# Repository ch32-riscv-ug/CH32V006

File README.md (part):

# CH32V006

<!-- This file is generated from ch32-riscv-ug/ch32-device-data (index/ + evidence/ + pipeline/build/build_readme.py). Edit there, not here. -->

[Choose a part](#product-comparison) &middot; [Documents](#documents) &middot; [Pin maps](#pin-maps--alternate-functions) &middot; [Pin viewer](https://ch32-riscv-ug.github.io/ch32-device-data/pins.html?chip=CH32M007) &middot; [Errata](#errata) &middot; [Examples](#evt-examples) &middot; [Address map](#address-map)

## Quick start

Programming and debug: **1-wire SDI** (WCH-Link, `Serial Debug Interface`).

### Debug / serial defaults

Where these land **without writing a remap register**. SWD is live at reset; the UART pads are not -- the pin must still be put into alternate-function mode. See `route` in evidence/README.ja.md.

| Series | SWDIO | SWCLK | UART TX | UART RX |
|---|---|---|---|---|
| CH32M007 | PD1 | PB3 | PD5 (USART1) | PD6 (USART1); PB3 (USART2) |
| CH32V002 | PD1 | - | PD5 (USART1) | PD6 (USART1) |
| CH32V004 | PD1 | - | PD5 (USART1) | PD6 (USART1) |
| CH32V005 | PD1 | PB3 | PD5 (USART1) | PD6 (USART1); PB3 (USART2) |
| CH32V006 | PD1 | PB3 | PD5 (USART1); PA7 (USART2) | PD6 (USART1); PB3 (USART2) |
| CH32V007 | PD1 | PB3 | PD5 (USART1); PA7 (USART2) | PD6 (USART1); PB3 (USART2) |

### Datasheets and reference manual

- CH32V002DS0.PDF (datasheet): [English](https://ch32-riscv-ug.github.io/CH32V006/datasheet_en/CH32V002DS0.PDF) · [中文](https://ch32-riscv-ug.github.io/CH32V006/datasheet_zh/CH32V002DS0.PDF)
- CH32V004DS0.PDF (datasheet): [English](https://ch32-riscv-ug.github.io/CH32V006/datasheet_en/CH32V004DS0.PDF) · [中文](https://ch32-riscv-ug.github.io/CH32V006/datasheet_zh/CH32V004DS0.PDF)
- CH32V006DS0.PDF (datasheet): [English](https://ch32-riscv-ug.github.io/CH32V006/datasheet_en/CH32V006DS0.PDF) · [中文](https://ch32-riscv-ug.github.io/CH32V006/datasheet_zh/CH32V006DS0.PDF)
- CH32V006DS2.PDF (datasheet): [中文](https://ch32-riscv-ug.github.io/CH32V006/datasheet_zh/CH32V006DS2.PDF)
- CH32V007DS0.PDF (datasheet): [English](https://ch32-riscv-ug.github.io/CH32V006/datasheet_en/CH32V007DS0.PDF) · [中文](https://ch32-riscv-ug.github.io/CH32V006/datasheet_zh/CH32V007DS0.PDF)
- CH32V00XRM.PDF (reference manual): [English](https://ch32-riscv-ug.github.io/CH32V006/datasheet_en/CH32V00XRM.PDF) · [中文](https://ch32-riscv-ug.github.io/CH32V006/datasheet_zh/CH32V00XRM.PDF)

## Series

Flash and SRAM list every value the series has; more than one means it varies by part number, and the per-part values are in the comparison table below.

| Series | Core | ISA | Flash | SRAM | Main clock | VDD | Packages | Products | Official |
|---|---|---|---|---|---|---|---|---|---|
| **CH32M007** | QingKe V2C | RV32EmC | 62K | 8K | 48 MHz | 2.0-5.5V | QFN26C3,QFN32,QSOP24,QSOP28 | 4 | [en](https://www.wch-ic.com/products/CH32M007.html) / [zh](https://www.wch.cn/products/CH32M007.html) |
| **CH32V002** | QingKe V2C | RV32EmC | 16K | 4K | 48 MHz | 2.0-5.5V | QFN12,QFN20,SOP16,SOP8,TSSOP20 | 5 | [en](https://www.wch-ic.com/products/CH32V002.html) / [zh](https://www.wch.cn/products/CH32V002.html) |
| **CH32V004** | QingKe V2C | RV32EmC | 32K | 6K | 48 MHz | 2.7-5.5V | QFN20L,TSSOP20 | 2 | [en](https://www.wch-ic.com/products/CH32V004.html) / [zh](https://www.wch.cn/products/CH32V004.html) |
| **CH32V005** | QingKe V2C | RV32EmC | 32K | 6K | 48 MHz | 2.0-5.5V | QFN12,QFN20,QSOP24,TSSOP20 | 4 | [en](https://www.wch-ic.com/products/CH32V005.html) / [zh](https://www.wch.cn/products/CH32V005.html) |
| **CH32V006** | QingKe V2C | RV32EmC | 16K/62K | 4K/8K | 48 MHz | 2.0-5.5V | QFN12,QFN20,QFN32,QSOP24,TSSOP20 | 8 | [en](https://www.wch-ic.com/products/CH32V006.html) / [zh](https://www.wch.cn/products/CH32V006.html) |
| **CH32V007** | QingKe V2C | RV32EmC | 62K | 8K | 48 MHz | 2.0-5.5V | QFN32,QSOP24 | 4 | [en](https://www.wch-ic.com/products/CH32V007.html) / [zh](https://www.wch.cn/products/CH32V007.html) |

## Product comparison

### CH32M007 product comparison

Only the 4 rows that differ between these 4 products; the other 14 are the same for all of them.

| | [CH32M007&#8203;E8R6](https://ch32-riscv-ug.github.io/ch32-device-data/pins.html?chip=CH32M007E8R6)&#8203;(QSOP24) | [CH32M007&#8203;E8U7](https://ch32-riscv-ug.github.io/ch32-device-data/pins.html?chip=CH32M007E8U7)&#8203;(QFN26C3) | [CH32M007&#8203;G8R6](https://ch32-riscv-ug.github.io/ch32-device-data/pins.html?chip=CH32M007G8R6)&#8203;(QSOP28) | [CH32M007&#8203;K8U7](https://ch32-riscv-ug.github.io/ch32-device-data/pins.html?chip=CH32M007K8U7)&#8203;(QFN32) |
|---|---|---|---|---|
| **GPIO** | 15 | 16 | 12 | 17 |
| **Temperature** | -40..85C | -40..105C | -40..85C | -40..105C |
| Three-phase pre-drive Voltage | 24V | 24V | 48V | 48V |
| Structure | P+N | P+N | N+N | N+N |

<details><summary>All 18 rows</summary>

| | [CH32M007&#8203;E8R6](https://ch32-riscv-ug.github.io/ch32-device-data/pins.html?chip=CH32M007E8R6)&#8203;(QSOP24) | [CH32M007&#8203;E8U7](https://ch32-riscv-ug.github.io/ch32-device-data/pins.html?chip=CH32M007E8U7)&#8203;(QFN26C3) | [CH32M007&#8203;G8R6](https://ch32-riscv-ug.github.io/ch32-device-data/pins.html?chip=CH32M007G8R6)&#8203;(QSOP28) | [CH32M007&#8203;K8U7](https://ch32-riscv-ug.github.io/ch32-device-data/pins.html?chip=CH32M007K8U7)&#8203;(QFN32) |
|---|---|---|---|---|
| **Flash** | 62K | 62K | 62K | 62K |
| **SRAM** | 8K | 8K | 8K | 8K |
| **GPIO** | 15 | 16 | 12 | 17 |
| **Temperature** | -40..85C | -40..105C | -40..85C | -40..105C |
| ADTM | 1 | 1 | 1 | 1 |
| GPTM | 1 | 1 | 1 | 1 |
| Streamlined timer | 1 | 1 | 1 | 1 |
| Watchdog | 2 | 2 | 2 | 2 |
| Three-phase pre-drive Voltage | 24V | 24V | 48V | 48V |
| Structure | P+N | P+N | N+N | N+N |
| ADC | 7+2 | 7+2 | 7+2 | 7+2 |
| Touch-key button | 7 | 7 | 7 | 7 |
| OPA | 1 | 1 | 1 | 1 |
| OPA Polling | 3 | 3 | 3 | 3 |
| CMP | 2 | 2 | 2 | 2 |
| Serial port | 2 | 2 | 2 | 2 |
| I2C | 1 | 1 | 1 | 1 |
| SPI | 1 | 1 | 1 | 1 |

</details>

### CH32V002 product comparison

Only the 3 rows that differ between these 5 products; the other 8 are the same for all of them.

| | [CH32V002&#8203;A4M6](https://ch32-riscv-ug.github.io/ch32-device-data/pins.html?chip=CH32V002A4M6)&#8203;(SOP16) | [CH32V002&#8203;D4U6](https://ch32-riscv-ug.github.io/ch32-device-data/pins.html?chip=CH32V002D4U6)&#8203;(QFN12) | [CH32V002&#8203;F4P6](https://ch32-riscv-ug.github.io/ch32-device-data/pins.html?chip=CH32V002F4P6)&#8203;(TSSOP20) | [CH32V002&#8203;F4U6](https://ch32-riscv-ug.github.io/ch32-device-data/pins.html?chip=CH32V002F4U6)&#8203;(QFN20) | [CH32V002&#8203;J4M6](https://ch32-riscv-ug.github.io/ch32-device-data/pins.html?chip=CH32V002J4M6)&#8203;(SOP8) |
|---|---|---|---|---|---|
| **GPIO** | 14 | 11 | 18 | 18 | 6 |
| ADC | 6+2 | 4+2 | 8+2 | 8+2 | 6+2 |
| SPI | 1 | - | 1 | 1 | - |

<details><summary>All 11 rows</summary>

| | [CH32V002&#8203;A4M6](https://ch32-riscv-ug.github.io/ch32-device-data/pins.html?chip=CH32V002A4M6)&#8203;(SOP16) | [CH32V002&#8203;D4U6](https://ch32-riscv-ug.github.io/ch32-device-data/pins.html?chip=CH32V002D4U6)&#8203;(QFN12) | [CH32V002&#8203;F4P6](https://ch32-riscv-ug.github.io/ch32-device-data/pins.html?chip=CH32V002F4P6)&#8203;(TSSOP20) | [CH32V002&#8203;F4U6](https://ch32-riscv-ug.github.io/ch32-device-data/pins.html?chip=CH32V002F4U6)&#8203;(QFN20) | [CH32V002&#8203;J4M6](https://ch32-riscv-ug.github.io/ch32-device-data/pins.html?chip=CH32V002J4M6)&#8203;(SOP8) |
|---|---|---|---|---|---|
| **Flash** | 16K | 16K | 16K | 16K | 16K |
| **SRAM** | 4K | 4K | 4K | 4K | 4K |
| **GPIO** | 14 | 11 | 18 | 18 | 6 |
| **Temperature** | -40..85C | -40..85C | -40..85C | -40..85C | -40..85C |
| ADTM | 1 | 1 | 1 | 1 | 1 |
| GPTM | 1 | 1 | 1 | 1 | 1 |
| Watchdog | 2 | 2 | 2 | 2 | 2 |
| ADC | 6+2 | 4+2 | 8+2 | 8+2 | 6+2 |
| Serial port | 1 | 1 | 1 | 1 | 1 |
| I2C | 1 | 1 | 1 | 1 | 1 |
| SPI | 1 | - | 1 | 1 | - |

</details>

### CH32V004 product comparison

| | [CH32V004&#8203;F6P1](https://ch32-riscv-ug.github.io/ch32-device-data/pins.html?chip=CH32V004F6P1)&#8203;(TSSOP20) | [CH32V004&#8203;F6U1](https://ch32-riscv-ug.github.io/ch32-device-data/pins.html?chip=CH32V004F6U1)&#8203;(QFN20L) |
|---|---|---|
| **Flash** | 32K | 32K |
| **SRAM** | 6K | 6K |
| **GPIO** | 18 | 18 |
| ADTM | 1 | 1 |
| GPTM | 1 | 1 |
| Watchdog | 2 | 2 |
| ADC | 8+2 | 8+2 |
| Serial port | 1 | 1 |
| I2C | 1 | 1 |
| SPI | 1 | 1 |

### CH32V005 product comparison

Only the 3 rows that differ between these 4 products; the other 9 are the same for all of them.

| | [CH32V005&#8203;D6U6](https://ch32-riscv-ug.github.io/ch32-device-data/pins.html?chip=CH32V005D6U6)&#8203;(QFN12) | [CH32V005&#8203;E6R6](https://ch32-riscv-ug.github.io/ch32-device-data/pins.html?chip=CH32V005E6R6)&#8203;(QSOP24) | [CH32V005&#8203;F6P6](https://ch32-riscv-ug.github.io/ch32-device-data/pins.html?chip=CH32V005F6P6)&#8203;(TSSOP20) | [CH32V005&#8203;F6U6](https://ch32-riscv-ug.github.io/ch32-device-data/pins.html?chip=CH32V005F6U6)&#8203;(QFN20) |
|---|---|---|---|---|
| **GPIO** | 11 | 22 | 18 | 18 |
| ADC | 4+2 | 8+2 | 8+2 | 8+2 |
| SPI | - | 1 | 1 | 1 |

<details><summary>All 12 rows</summary>

| | [CH32V005&#8203;D6U6](https://ch32-riscv-ug.github.io/ch32-device-data/pins.html?chip=CH32V005D6U6)&#8203;(QFN12) | [CH32V005&#8203;E6R6](https://ch32-riscv-ug.github.io/ch32-device-data/pins.html?chip=CH32V005E6R6)&#8203;(QSOP24) | [CH32V005&#8203;F6P6](https://ch32-riscv-ug.github.io/ch32-device-data/pins.html?chip=CH32V005F6P6)&#8203;(TSSOP20) | [CH32V005&#8203;F6U6](https://ch32-riscv-ug.github.io/ch32-device-data/pins.html?chip=CH32V005F6U6)&#8203;(QFN20) |
|---|---|---|---|---|
| **Flash** | 32K | 32K | 32K | 32K |
| **SRAM** | 6K | 6K | 6K | 6K |
| **GPIO** | 11 | 22 | 18 | 18 |
| **Temperature** | -40..85C | -40..85C | -40..85C | -40..85C |
| ADTM | 1 | 1 | 1 | 1 |
| GPTM | 1 | 1 | 1 | 1 |
| Watchdog | 2 | 2 | 2 | 2 |
| ADC | 4+2 | 8+2 | 8+2 | 8+2 |
| OPA | 1 | 1 | 1 | 1 |
| Serial port | 2 | 2 | 2 | 2 |
| I2C | 1 | 1 | 1 | 1 |
| SPI | - | 1 | 1 | 1 |

</details>

### CH32V006 product comparison

CH32V006K8U6 is not in the datasheet's comparison table, so it has no column here; every value it does have is in `index/products.csv`.

Only the 10 rows that differ between these 7 products; the other 5 are the same for all of them.

| | [CH32V006&#8203;D8U7](https://ch32-riscv-ug.github.io/ch32-device-data/pins.html?chip=CH32V006D8U7)&#8203;(QFN12) | [CH32V006&#8203;E8R6](https://ch32-riscv-ug.github.io/ch32-device-data/pins.html?chip=CH32V006E8R6)&#8203;(QSOP24) | [CH32V006&#8203;E8R7](https://ch32-riscv-ug.github.io/ch32-device-data/pins.html?chip=CH32V006E8R7)&#8203;(QSOP24) | [CH32V006&#8203;F4U6](https://ch32-riscv-ug.github.io/ch32-device-data/pins.html?chip=CH32V006F4U6)&#8203;(QFN20) | [CH32V006&#8203;F8P7](https://ch32-riscv-ug.github.io/ch32-device-data/pins.html?chip=CH32V006F8P7)&#8203;(TSSOP20) | [CH32V006&#8203;F8U7](https://ch32-riscv-ug.github.io/ch32-device-data/pins.html?chip=CH32V006F8U7)&#8203;(QFN20) | [CH32V006&#8203;K8U7](https://ch32-riscv-ug.github.io/ch32-device-data/pins.html?chip=CH32V006K8U7)&#8203;(QFN32) |
|---|---|---|---|---|---|---|---|
| **Flash** | 62K | 62K | 62K | 16K | 62K | 62K | 62K |
| **SRAM** | 8K | 8K | 8K | 4K | 8K | 8K | 8K |
| **GPIO** | 11 | 22 | 22 | 18 | 18 | 18 | 31 |
| **Temperature** | -40..105C | -40..85C | -40..105C | -40..85C | -40..105C | -40..105C | -40..105C |
| ADC | 4+2 | 8+2 | 8+2 | 8+2 | 8+2 | 8+2 | 8+2 |
| Capacitive touchkey | 4 | 8 | 8 | 8 | 8 | 8 | 8 |
| OPA | 1 | 1 | 1 | - | 1 | 1 | 1 |
| Serial port | 2 | 2 | 2 | 1 | 2 | 2 | 2 |
| OPA polling | 3 | 3 | 3 | - | 3 | 3 | 3 |
| SPI | - | 1 | 1 | 1 | 1 | 1 | 1 |

<details><summary>All 15 rows</summary>

| | [CH32V006&#8203;D8U7](https://ch32-riscv-ug.github.io/ch32-device-data/pins.html?chip=CH32V006D8U7)&#8203;(QFN12) | [CH32V006&#8203;E8R6](https://ch32-riscv-ug.github.io/ch32-device-data/pins.html?chip=CH32V006E8R6)&#8203;(QSOP24) | [CH32V006&#8203;E8R7](https://ch32-riscv-ug.github.io/ch32-device-data/pins.html?chip=CH32V006E8R7)&#8203;(QSOP24) | [CH32V006&#8203;F4U6](https://ch32-riscv-ug.github.io/ch32-device-data/pins.html?chip=CH32V006F4U6)&#8203;(QFN20) | [CH32V006&#8203;F8P7](https://ch32-riscv-ug.github.io/ch32-device-data/pins.html?chip=CH32V006F8P7)&#8203;(TSSOP20) | [CH32V006&#8203;F8U7](https://ch32-riscv-ug.github.io/ch32-device-data/pins.html?chip=CH32V006F8U7)&#8203;(QFN20) | [CH32V006&#8203;K8U7](https://ch32-riscv-ug.github.io/ch32-device-data/pins.html?chip=CH32V006K8U7)&#8203;(QFN32) |
|---|---|---|---|---|---|---|---|
| **Flash** | 62K | 62K | 62K | 16K | 62K | 62K | 62K |
| **SRAM** | 8K | 8K | 8K | 4K | 8K | 8K | 8K |
| **GPIO** | 11 | 22 | 22 | 18 | 18 | 18 | 31 |
| **Temperature** | -40..105C | -40..85C | -40..105C | -40..85C | -40..105C | -40..105C | -40..105C |
| ADTM | 1 | 1 | 1 | 1 | 1 | 1 | 1 |
| GPTM | 1 | 1 | 1 | 1 | 1 | 1 | 1 |
| Streamlined timer | 1 | 1 | 1 | 1 | 1 | 1 | 1 |
| Watchdog | 2 | 2 | 2 | 2 | 2 | 2 | 2 |
| ADC | 4+2 | 8+2 | 8+2 | 8+2 | 8+2 | 8+2 | 8+2 |
| Capacitive touchkey | 4 | 8 | 8 | 8 | 8 | 8 | 8 |
| OPA | 1 | 1 | 1 | - | 1 | 1 | 1 |
| Serial port | 2 | 2 | 2 | 1 | 2 | 2 | 2 |
| OPA polling | 3 | 3 | 3 | - | 3 | 3 | 3 |
| I2C | 1 | 1 | 1 | 1 | 1 | 1 | 1 |
| SPI | - | 1 | 1 | 1 | 1 | 1 | 1 |

</details>

### CH32V007 product comparison

Only the 2 rows that differ between these 4 products; the other 14 are the same for all of them.

| | [CH32V007&#8203;E8R6](https://ch32-riscv-ug.github.io/ch32-device-data/pins.html?chip=CH32V007E8R6)&#8203;(QSOP24) | [CH32V007&#8203;E8R7](https://ch32-riscv-ug.github.io/ch32-device-data/pins.html?chip=CH32V007E8R7)&#8203;(QSOP24) | [CH32V007&#8203;K8U6](https://ch32-riscv-ug.github.io/ch32-device-data/pins.html?chip=CH32V007K8U6)&#8203;(QFN32) | [CH32V007&#8203;K8U7](https://ch32-riscv-ug.github.io/ch32-device-data/pins.html?chip=CH32V007K8U7)&#8203;(QFN32) |
|---|---|---|---|---|
| **GPIO** | 22 | 22 | 31 | 31 |
| **Temperature** | -40..85C | -40..105C | -40..85C | -40..105C |

<details><summary>All 16 rows</summary>

| | [CH32V007&#8203;E8R6](https://ch32-riscv-ug.github.io/ch32-device-data/pins.html?chip=CH32V007E8R6)&#8203;(QSOP24) | [CH32V007&#8203;E8R7](https://ch32-riscv-ug.github.io/ch32-device-data/pins.html?chip=CH32V007E8R7)&#8203;(QSOP24) | [CH32V007&#8203;K8U6](https://ch32-riscv-ug.github.io/ch32-device-data/pins.html?chip=CH32V007K8U6)&#8203;(QFN32) | [CH32V007&#8203;K8U7](https://ch32-riscv-ug.github.io/ch32-device-data/pins.html?chip=CH32V007K8U7)&#8203;(QFN32) |
|---|---|---|---|---|
| **Flash** | 62K | 62K | 62K | 62K |
| **SRAM** | 8K | 8K | 8K | 8K |
| **GPIO** | 22 | 22 | 31 | 31 |
| **Temperature** | -40..85C | -40..105C | -40..85C | -40..105C |
| ADTM | 1 | 1 | 1 | 1 |
| GPTM | 1 | 1 | 1 | 1 |
| Streamlined timer | 1 | 1 | 1 | 1 |
| Watchdog | 2 | 2 | 2 | 2 |
| ADC | 8+2 | 8+2 | 8+2 | 8+2 |
| Touch-key button | 8 | 8 | 8 | 8 |
| OPA | 1 | 1 | 1 | 1 |
| OPA Polling | 3 | 3 | 3 | 3 |
| CMP | 2 | 2 | 2 | 2 |
| Serial port | 2 | 2 | 2 | 2 |
| I2C | 1 | 1 | 1 | 1 |
| SPI | 1 | 1 | 1 | 1 |

</details>

## Block diagrams

### CH32M007

System block diagram from the [WCH product page](https://www.wch-ic.com/products/CH32M007.html).

<details><summary>Internal block diagram (datasheet)</summary>

</details>

### CH32V002

System block diagram from the [WCH product page](https://www.wch-ic.com/products/CH32V002.html).

<details><summary>Internal block diagram (datasheet)</summary>

</details>

### CH32V004

System block diagram from the [WCH product page](https://www.wch-ic.com/products/CH32V004.html).

<details><summary>Internal block diagram (datasheet)</summary>

</details>

### CH32V005

System block diagram from the [WCH product page](https://www.wch-ic.com/products/CH32V005.html).

<details><summary>Internal block diagram (datasheet)</summary>

</details>

### CH32V006

System block diagram from the [WCH product page](https://www.wch-ic.com/products/CH32V006.html).

<details><summary>Internal block diagram (datasheet)</summary>

</details>

### CH32V007

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
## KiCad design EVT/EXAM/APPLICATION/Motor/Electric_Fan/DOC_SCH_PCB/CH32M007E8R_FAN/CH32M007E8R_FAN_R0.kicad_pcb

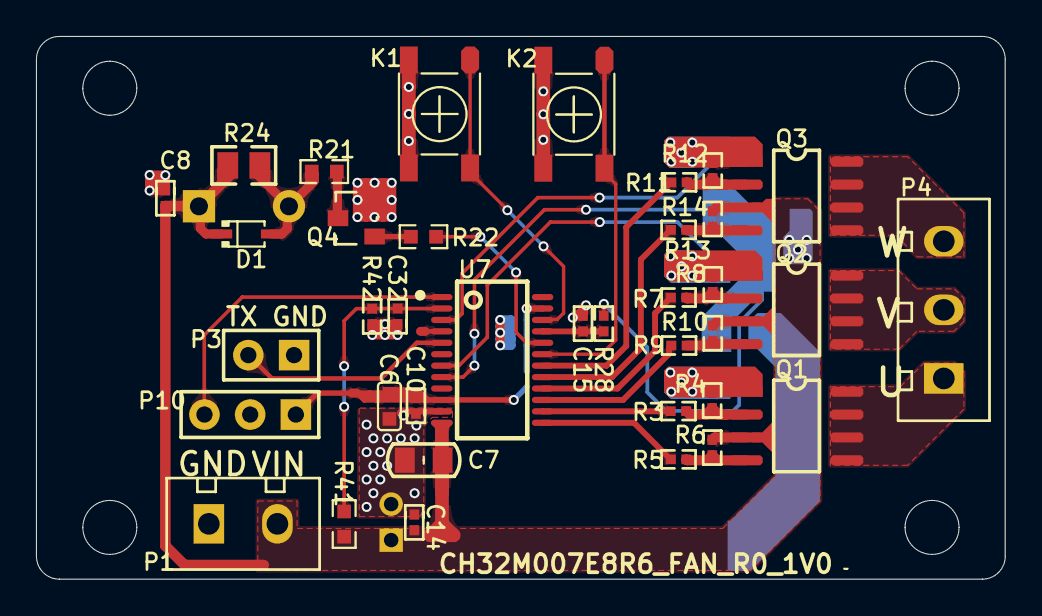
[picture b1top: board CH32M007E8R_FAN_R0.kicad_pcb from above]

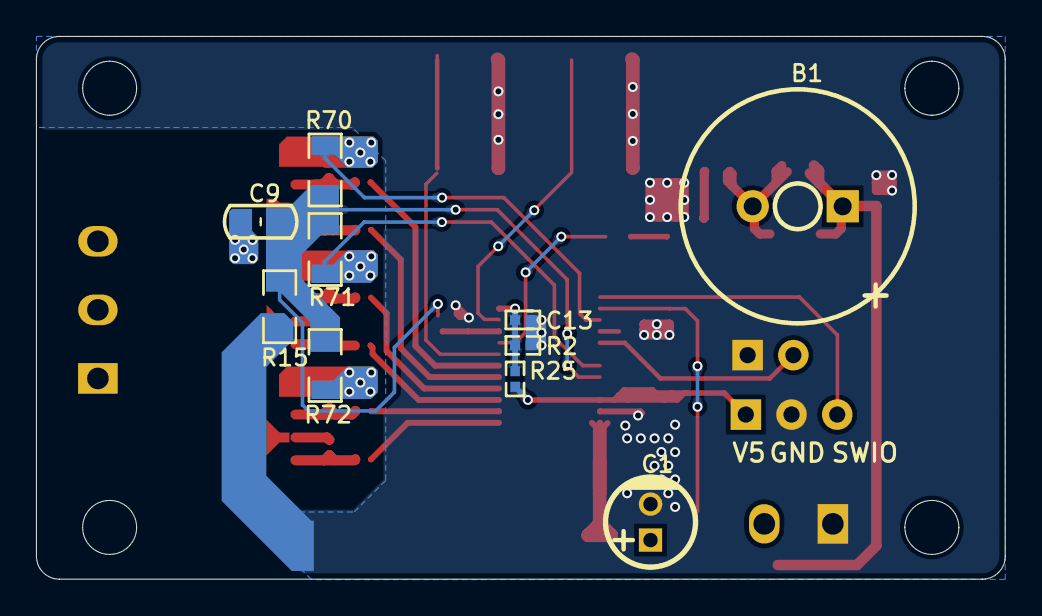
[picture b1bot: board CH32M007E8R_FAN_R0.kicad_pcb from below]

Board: 2 copper layers, 53.8 x 30.2 mm, 47 parts (10 on the bottom side), 33 nets.

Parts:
B1: BUZZER; M_BUZZER12550
C1: 47uF/35V; M_C_RB_D5F2
C6: 10uF; M_C0603
C7: 10uF/25V; M_C0805
C8: 0.1uF/25V; M_C0402-
C9: 1uF/50V; M_C0805
C10, C13, C32: 0.1uF; M_C0402-
C14: 0.1uF/50V; M_C0402-
C15: 1nF; M_C0402-
D1: 4148; SOD-323
K1, K2: KH-6X6X8H-STM; KEY2-SMD
P1: POWER; WJ15EDGRC3.81-2
P3: TXD; HDR2.54-LI-2P
P4: MHDR1X3; WJ15EDGRC3.81-3
P10: SWD; HDR2.54-LI-3P
Q1, Q2, Q3: NP4606SR; SOP8
Q4: S8050; SOT23
R2, R42: 1k 1%; M_R0402-
R3, R5, R7, R9, R11, R13: 22 Ω; M_R0402-
R4, R6, R8, R10, R12, R14: 20k; M_R0402-
R15, R70, R71, R72: 0R100/1W; M_R1206-
R21: 100Ω; M_R0603
R22: 1kΩ; M_R0603
R24: 2KΩ; M_R0805
R25: 15k 1%; M_R0402-
R28: 10k; M_R0402-
R41: 4.7k 1%; M_R0603
U7: CH32M007E8R6; QSOP24

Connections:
ADC_Vbus: C32.1, R41.1, R42.2, U7.2
BEEP_CTRL: R22.2, U7.20
CMP1_N0: C15.2, R28.2, U7.21
CMP1_P0: C13.1, R2.2, R25.1, U7.23
GND: C1.2, C6.2, C7.2, C8.2, C10.2, C13.2, C14.2, C15.1, C32.2, K1.3, K1.4, K2.3, K2.4, P1.1, P3.1, P10.2, Q4.2, R2.1, R15.1, R42.1, U7.11
I1_shunt: C9.2, R15.2, R28.1, R70.1, R71.1, R72.1, U7.8
KEY1: K1.1, K1.2, U7.22
KEY2: K2.1, K2.2, U7.19
M1_CH1_H: R5.2, U7.13
M1_CH1_L: R3.2, U7.14
M1_CH2_H: R9.2, U7.15
M1_CH2_L: R7.2, U7.16
M1_CH3_H: R13.2, U7.17
M1_CH3_L: R11.2, U7.18
M1_Iu: Q1.1, R4.1, R72.2
M1_Iv: Q2.1, R8.1, R71.2, U7.7
M1_Iw: Q3.1, R12.1, R70.2, U7.3
M1_U: P4.1, Q1.5, Q1.6, Q1.7, Q1.8
M1_V: P4.2, Q2.5, Q2.6, Q2.7, Q2.8
M1_W: P4.3, Q3.5, Q3.6, Q3.7, Q3.8
NetB1_2: B1.2, D1.1, R21.2, R24.1
NetQ1_2: Q1.2, R3.1, R4.2
NetQ1_4: Q1.4, R5.1, R6.2
NetQ2_2: Q2.2, R7.1, R8.2
NetQ2_4: Q2.4, R9.1, R10.2
NetQ3_2: Q3.2, R11.1, R12.2
NetQ3_4: Q3.4, R13.1, R14.2
NetQ4_1: Q4.1, R22.1
NetQ4_3: Q4.3, R21.1
SWIO: P10.3, U7.1
UART1_TX: P3.2, U7.5
V5: C6.1, C10.1, P10.1, R25.2, U7.10
Vin: B1.1, C1.1, C7.1, C8.1, C9.1, C14.1, D1.2, P1.2, Q1.3, Q2.3, Q3.3, R6.1, R10.1, R14.1, R24.2, R41.2, U7.12

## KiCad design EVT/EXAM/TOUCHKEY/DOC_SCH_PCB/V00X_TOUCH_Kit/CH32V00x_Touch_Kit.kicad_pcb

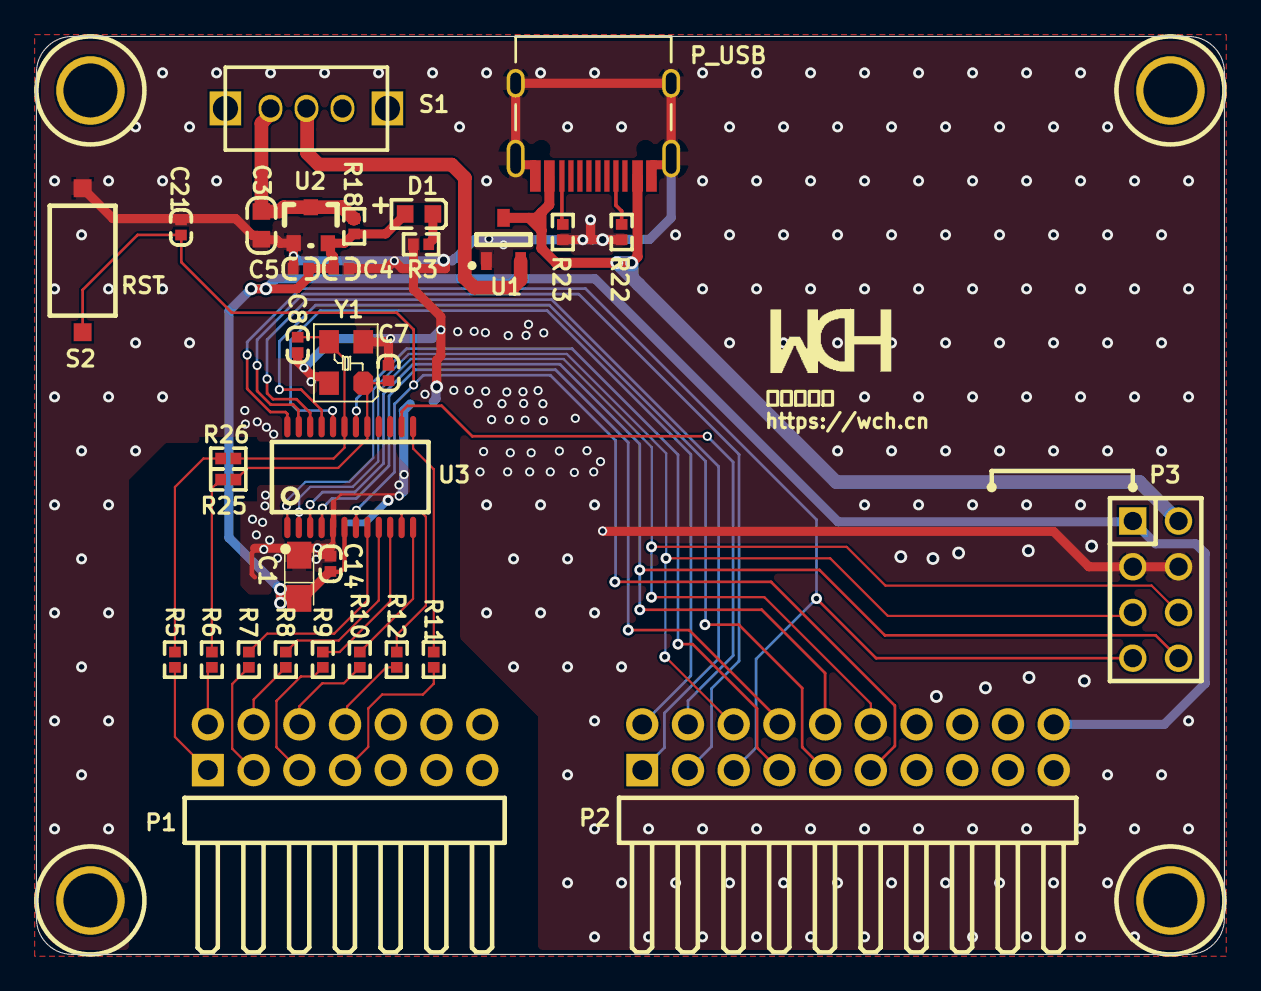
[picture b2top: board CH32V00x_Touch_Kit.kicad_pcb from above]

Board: 2 copper layers, 66.0 x 51.0 mm, 33 parts (0 on the bottom side), 38 nets.

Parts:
C1: 10uF; CASE-A_3216
C3: 10uF; 0603_C
C4: 2.2uF; 0402_C
C5, C14, C21: 0.1uF; 0402_C
C7, C8: NC(22pF); 0402_C
D1: power; 0603+
P1: Header 7X2; HDR-TH_14P-P2.54-H-M-R2-C10-S2.54
P2: Header 10X2; HDR-TH_20P-P2.54-H-M-R2-C10-S2.54
P3: Header 4X2; IDC8-2.54mm
P_USB: TYPE-C; TYPE-C-Receptacle-2.0
R3: 1K; 0402
R5, R6, R7, R8, R9, R10, R11, R12: 0Ω(560Ω); 0402
R18: NC(0R); 0402
R22, R23: 5.1K; 0402
R25, R26: 0R; 0402
S1: SW SPDT; SW1
S2: RST; SMD_6.1x3.65x2.5mm-KEY
U1: CH213; SOT-23-3
U2: 6219P33M; SOT-23
U3: CH32V006E8R6; QSOP24
Y1: NC(24MHz); XT3225

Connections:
3V3: C1.1, C4.1, C5.1, C14.2, D1.1, P2.20, P3.1, R18.1, U2.2, U3.6
+5V: P3.2, P_USB.A4, P_USB.B4, U1.3
GND: C1.2, C3.2, C4.2, C5.2, C7.1, C8.1, C14.1, C21.1, P2.19, P3.3, P3.4, P_USB.0, P_USB.A1, P_USB.B1, R3.2, R22.2, R23.2, S2.1, U1.1, U2.1, U3.5, Y1.2, Y1.4
NRST: C21.2, P2.11, S2.2, U3.7
NetD1_2: D1.2, R3.1
NetP_USB_A5: P_USB.A5, R22.1
NetP_USB_B5: P_USB.B5, R23.1
NetS1_1: S1.1, U1.2
PA0: P2.7, U3.18
PA1: R6.2, R25.2
PA2: R5.1, R26.2
PA3: P2.9, U3.21
PB0: P2.1, U3.22
PB1: P2.3, U3.23
PB3: P2.5, P3.7, U3.24
PC0: P2.12, P3.6, U3.2
PC1: P2.10, P3.8, U3.3
PC2: P2.8, U3.4
PC4: R7.1, U3.8
PD0: P2.2, U3.20
PD1: P2.6, P3.5, U3.1
PD2: R8.2, U3.9
PD3: R9.1, U3.10
PD4: R12.2, U3.11
PD5: R10.2, U3.12
PD6: R11.1, U3.13
PD7: P2.4, U3.14
TS0: P1.1, R5.2
TS1: P1.2, R6.1
TS2: P1.3, R7.2
TS3: P1.4, R8.1
TS4: P1.5, R9.2
TS5: P1.6, R10.1
TS6: P1.7, R11.2
TS7: P1.8, R12.1
V5V: C3.1, R18.2, S1.2, U2.3
XI: C7.2, R25.1, U3.17, Y1.1
XO: C8.2, R26.1, U3.19, Y1.3

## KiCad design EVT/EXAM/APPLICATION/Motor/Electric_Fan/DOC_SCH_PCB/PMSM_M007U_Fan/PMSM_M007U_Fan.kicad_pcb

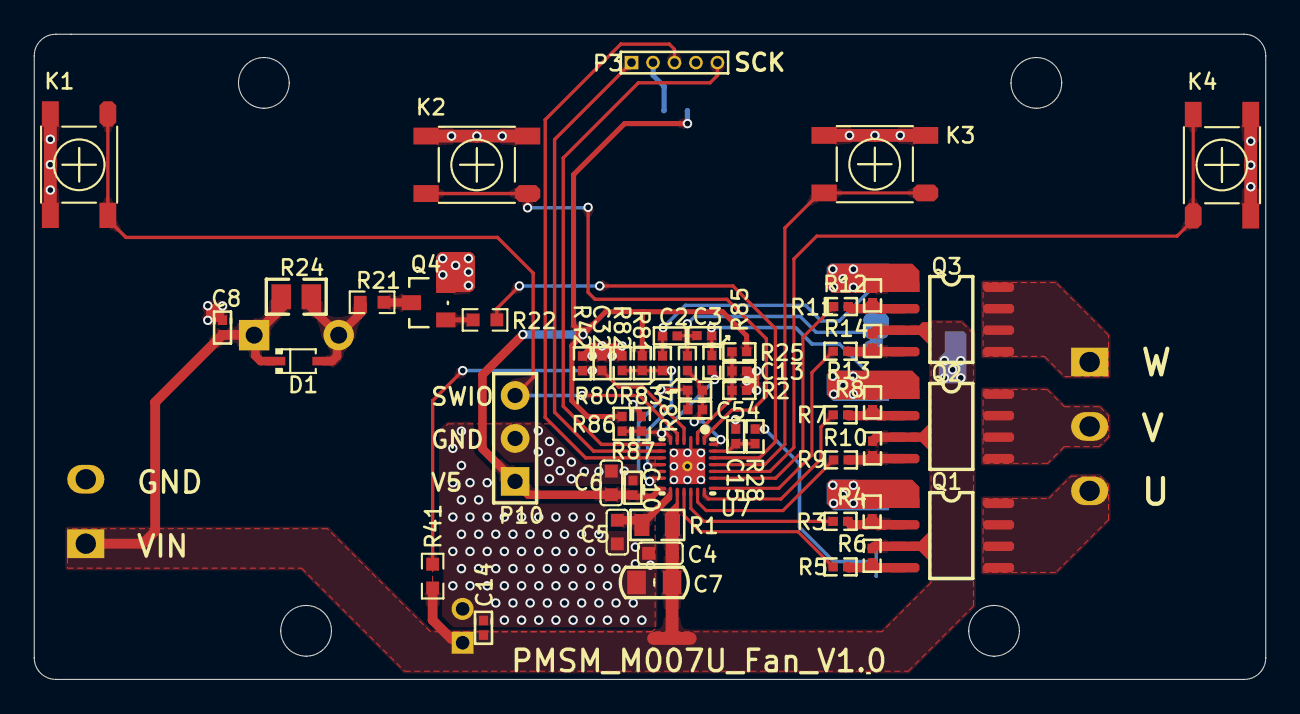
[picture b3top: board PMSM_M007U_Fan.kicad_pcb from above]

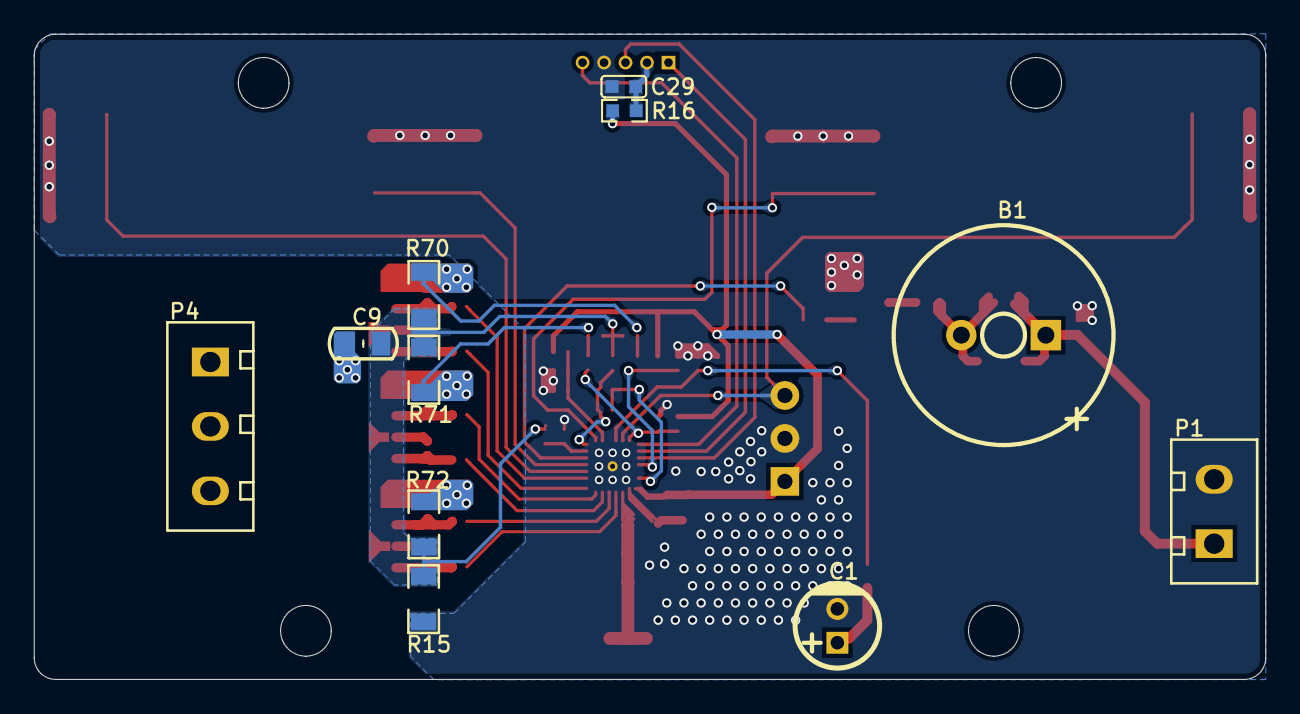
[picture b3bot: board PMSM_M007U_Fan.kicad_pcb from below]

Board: 2 copper layers, 72.8 x 38.2 mm, 65 parts (11 on the bottom side), 42 nets.

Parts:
B1: BUZZER; M_BUZZER12550
C1: 47uF/35V; M_C_RB_D5F2
C2, C3: 100pF; M_C0402-
C4: NC; M_C0603
C5: 2.2uF/25V; M_C0603
C6, C29: 10uF; M_C0603
C7: 10uF/25V; M_C0805
C8: 0.1uF/25V; M_C0402-
C9: 1uF/50V; M_C0805
C10, C13, C32: 0.1uF; M_C0402-
C14: 0.1uF/50V; M_C0402-
C15: 1nF; M_C0402-
C54: NC; M_C0402-
D1: 4148; SOD-323
K1, K2, K3, K4: KH-6X6X8H-STM; KEY2-SMD
P1: POWER; WJ15EDGRC3.81-2
P3: 5PIN; M_PIN1.27_5P
P4: MHDR1X3; WJ15EDGRC3.81-3
P10: SWD; HDR2.54-LI-3P
Q1, Q2, Q3: SOP8
Q4: S8050; SOT23
R1: 100 Ω; M_R0805-
R2: 1k 1%; M_R0402-
R3, R5, R7, R9, R11, R13: 47 Ω; M_R0402-
R4, R8, R12: 20k; M_R0402-
R6, R10, R14: NC /(20k); M_R0402-
R15, R70, R71, R72: 0R100/1W; M_R1206-
R16: 0Ω / NC; M_R0603
R21: 100Ω; M_R0603
R22: 1kΩ; M_R0603
R24: 2kΩ; M_R0805
R25: 15k 1%; M_R0402-
R28: 10k; M_R0402-
R41: 4.7k 1%; M_R0603
R42: 1.5k 1%; M_R0402-
R80, R83, R85: 2.4k 1%; M_R0402-
R81, R86: 30k 1%; M_R0402-
R82, R87: 10k 1%; M_R0402-
R84: 7.5k 1%; M_R0402-
U7: CH32M007E8U; QFN26C_3X3

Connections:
ADC_I1: C54.1, R84.2, U7.12
ADC_Vbus: C32.1, R41.1, R42.2, U7.4
BEEP_CTRL: R22.2, U7.24
CMP1_N0: C15.2, R28.2, U7.25
CMP1_P0: C13.1, R2.2, R25.1, U7.2
GND: C1.2, C4.2, C5.2, C6.2, C7.2, C8.2, C10.2, C13.2, C14.2, C15.1, C29.2, C32.2, K1.3, K1.4, K2.3, K2.4, K3.3, K3.4, K4.3, K4.4, P1.2, P3.4, P10.2, Q4.2, R2.1, R15.1, R42.1, R82.1, R87.1, U7.0, U7.3
I1_shunt: C2.1, C3.1, C9.2, R15.2, R28.1, R70.1, R71.1, R72.1, R83.1
KEY2: K2.1, K2.2, U7.1
KEY3: K3.1, K3.2, U7.23
KEY4: K4.1, K4.2, U7.22
M1_CH1_H: R5.2, U7.16
M1_CH1_L: R3.2, U7.17
M1_CH2_H: R9.2, U7.18
M1_CH2_L: R7.2, U7.19
M1_CH3_H: R13.2, U7.20
M1_CH3_L: R11.2, U7.21
M1_Iu: Q1.1, R4.1, R72.2
M1_Iv: C3.2, Q2.1, R8.1, R71.2, R85.1
M1_Iw: C2.2, Q3.1, R12.1, R70.2, R80.1
M1_U: P4.3, Q1.5, Q1.6, Q1.7, Q1.8
M1_V: P4.2, Q2.5, Q2.6, Q2.7, Q2.8
M1_W: P4.1, Q3.5, Q3.6, Q3.7, Q3.8
M_CS: P3.1, U7.8
M_MOSI: P3.3, U7.9
M_SCK: P3.5, U7.7
NetB1_2: B1.2, D1.1, R21.2, R24.1
NetC5_1: C5.1, R1.1, U7.14
NetQ1_2: Q1.2, R3.1, R4.2
NetQ1_4: Q1.4, R5.1, R6.2
NetQ2_2: Q2.2, R7.1, R8.2
NetQ2_4: Q2.4, R9.1, R10.2
NetQ3_2: Q3.2, R11.1, R12.2
NetQ3_4: Q3.4, R13.1, R14.2
NetQ4_1: Q4.1, R22.1
NetQ4_3: Q4.3, R21.1
OPA_N0: C54.2, R83.2, R84.1, U7.26
OPA_P1: R80.2, R81.2, R82.2, U7.10
OPA_P2: R85.2, R86.2, R87.2, U7.6
SWIO: K1.1, K1.2, P10.3, U7.5
V5: C6.1, C10.1, P10.1, R16.2, R25.2, R81.1, R86.1, U7.13
VCC2: C29.1, P3.2, R16.1
Vin: B1.1, C1.1, C4.1, C7.1, C8.1, C9.1, C14.1, D1.2, P1.1, Q1.3, Q2.3, Q3.3, R1.2, R6.1, R10.1, R14.1, R24.2, R41.2, U7.15

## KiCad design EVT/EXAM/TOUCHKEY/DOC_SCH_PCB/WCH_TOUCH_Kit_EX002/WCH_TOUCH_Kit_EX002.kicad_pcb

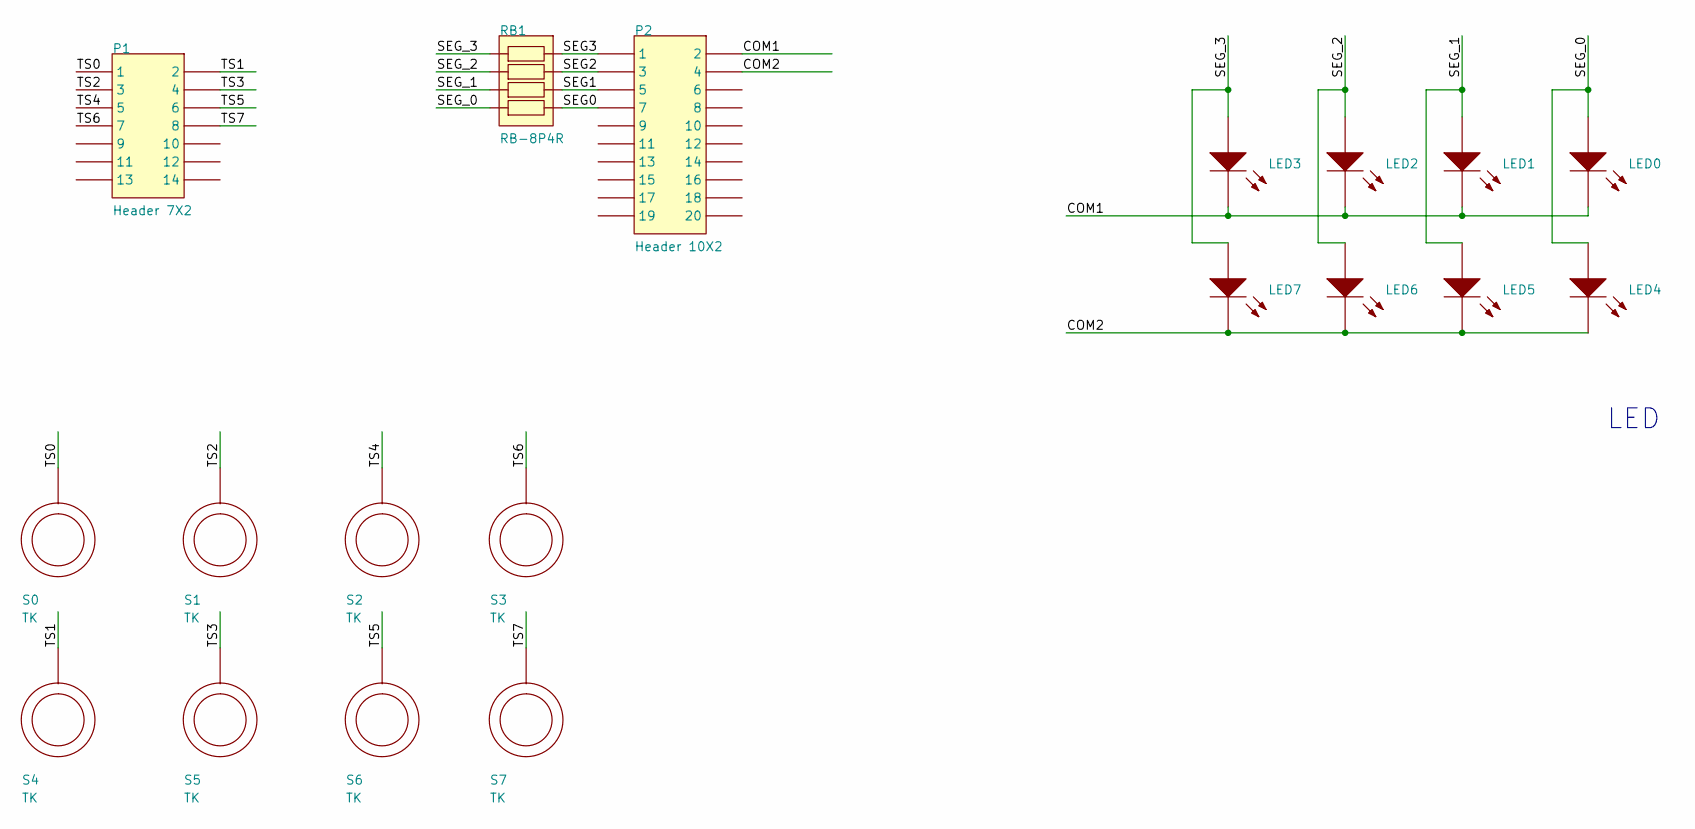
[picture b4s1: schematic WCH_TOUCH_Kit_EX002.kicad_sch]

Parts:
LED0, LED1, LED2, LED3, LED4, LED5, LED6, LED7: LED0805-RD_EH
P1: Header 7X2; HDR-TH_14P-P2.54-H-F-R2-C10-W8.5
P2: Header 10X2; HDR-TH_20P-P2.54-H-F-R2-C10-W8.5
RB1: RB-8P4R; RCA-8P4R-0603
S0, S1, S2, S3, S4, S5, S6, S7: TK; TOUCHKEY-12mm-S

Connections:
COM1: LED0.2 (K), LED1.2 (K), LED2.2 (K), LED3.2 (K), P2.2
COM2: LED4.2 (K), LED5.2 (K), LED6.2 (K), LED7.2 (K), P2.4
SEG0: P2.7, RB1.4
SEG1: P2.5, RB1.3
SEG2: P2.3, RB1.2
SEG3: P2.1, RB1.1
SEG_0: LED0.1 (A), LED4.1 (A), RB1.5
SEG_1: LED1.1 (A), LED5.1 (A), RB1.6
SEG_2: LED2.1 (A), LED6.1 (A), RB1.7
SEG_3: LED3.1 (A), LED7.1 (A), RB1.8
TS0: P1.1, S0.1
TS1: P1.2, S4.1
TS2: P1.3, S1.1
TS3: P1.4, S5.1
TS4: P1.5, S2.1
TS5: P1.6, S6.1
TS6: P1.7, S3.1
TS7: P1.8, S7.1

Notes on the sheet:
LED

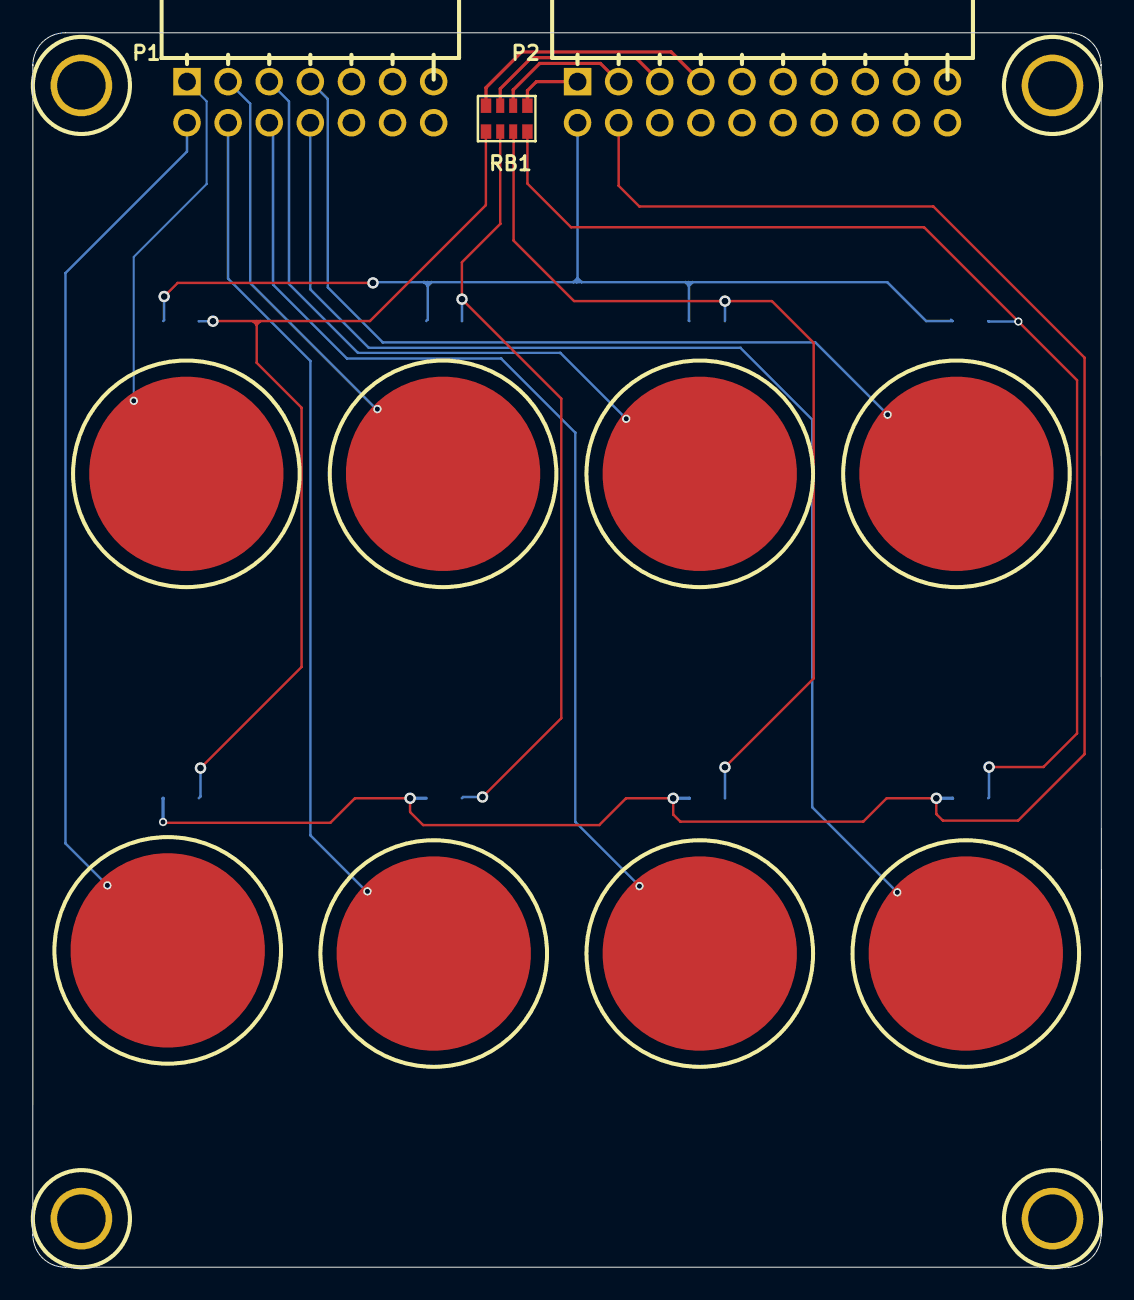
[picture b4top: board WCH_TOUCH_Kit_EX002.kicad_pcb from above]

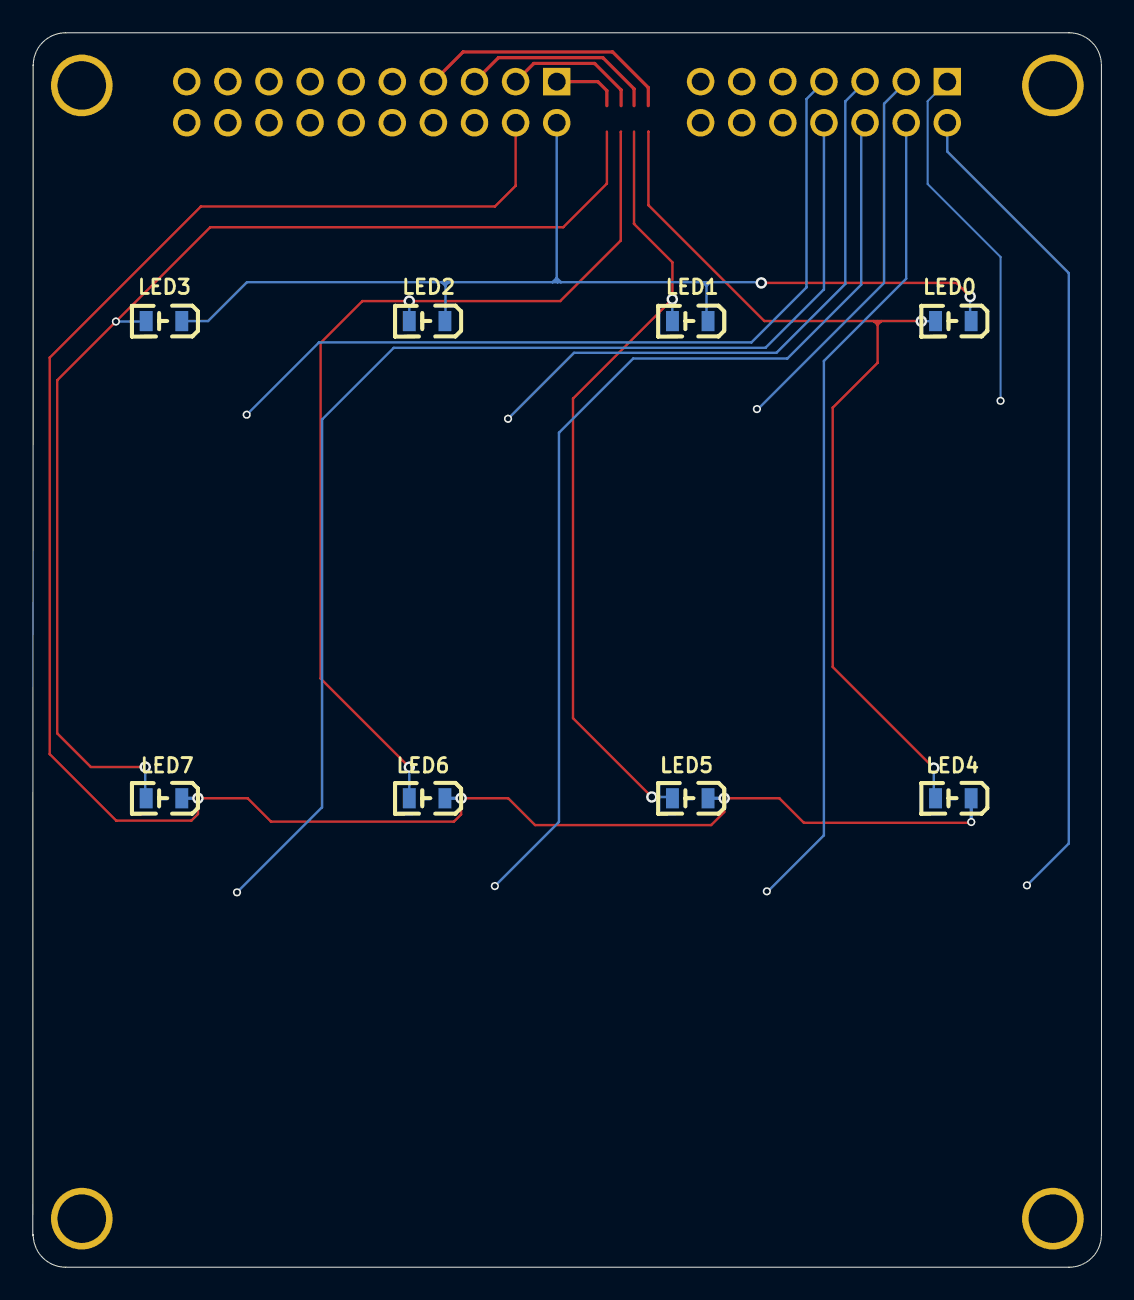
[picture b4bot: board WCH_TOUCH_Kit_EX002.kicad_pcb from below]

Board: 2 copper layers, 66.0 x 76.3 mm, 19 parts (8 on the bottom side), 18 nets.

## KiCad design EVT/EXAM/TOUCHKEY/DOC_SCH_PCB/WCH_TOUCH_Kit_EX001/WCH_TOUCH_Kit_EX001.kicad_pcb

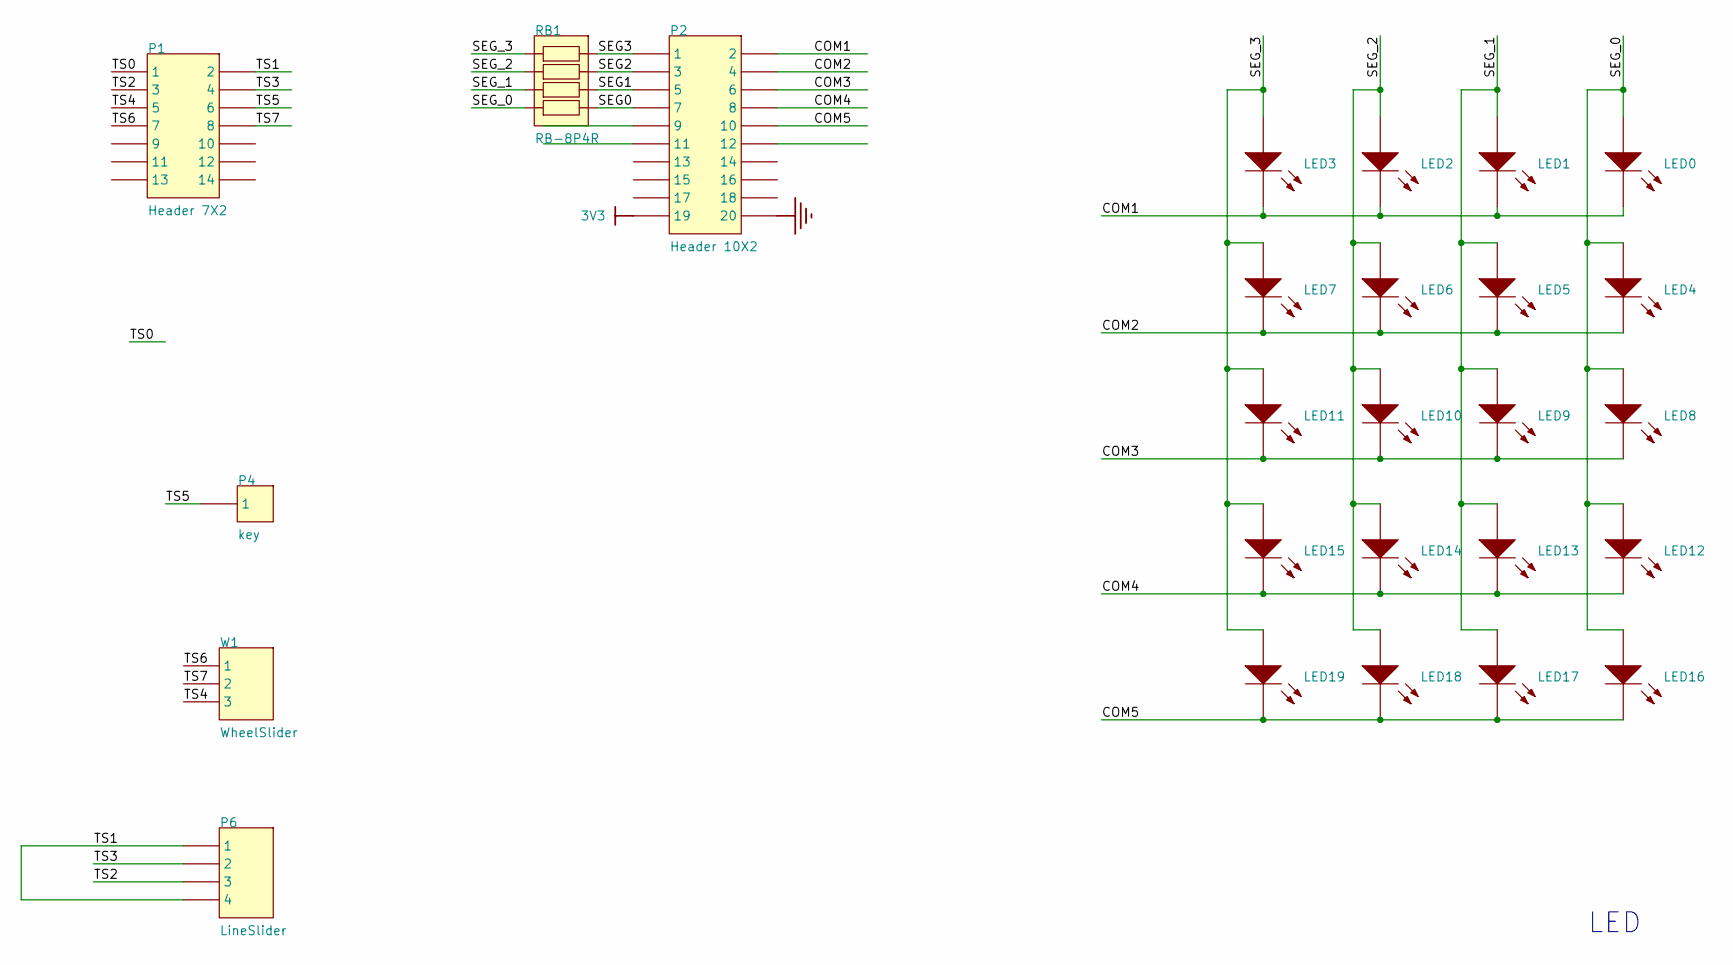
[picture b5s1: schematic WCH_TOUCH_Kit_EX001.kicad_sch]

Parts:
LED0, LED1, LED2, LED3, LED4, LED5, LED6, LED7, LED8, LED9, LED10, LED11, LED12, LED13, LED14, LED15, LED16, LED17, LED18, LED19: LED0805-RD_EH
P1: Header 7X2; HDR-TH_14P-P2.54-H-F-R2-C10-W8.5
P2: Header 10X2; HDR-TH_20P-P2.54-H-F-R2-C10-W8.5
P4: key
P6: LineSlider; Slider_4_46X8.5
RB1: RB-8P4R; RCA-8P4R-0603
W1: WheelSlider; 滑轮10-18-3

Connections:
3V3: P2.19
COM1: LED0.2 (K), LED1.2 (K), LED2.2 (K), LED3.2 (K), P2.2
COM2: LED4.2 (K), LED5.2 (K), LED6.2 (K), LED7.2 (K), P2.4
COM3: LED8.2 (K), LED9.2 (K), LED10.2 (K), LED11.2 (K), P2.6
COM4: LED12.2 (K), LED13.2 (K), LED14.2 (K), LED15.2 (K), P2.8
COM5: LED16.2 (K), LED17.2 (K), LED18.2 (K), LED19.2 (K), P2.10
GND: P2.20
SEG0: P2.7, RB1.4
SEG1: P2.5, RB1.3
SEG2: P2.3, RB1.2
SEG3: P2.1, RB1.1
SEG_0: LED0.1 (A), LED4.1 (A), LED8.1 (A), LED12.1 (A), LED16.1 (A), RB1.5
SEG_1: LED1.1 (A), LED5.1 (A), LED9.1 (A), LED13.1 (A), LED17.1 (A), RB1.6
SEG_2: LED2.1 (A), LED6.1 (A), LED10.1 (A), LED14.1 (A), LED18.1 (A), RB1.7
SEG_3: LED3.1 (A), LED7.1 (A), LED11.1 (A), LED15.1 (A), LED19.1 (A), RB1.8
TS0: P1.1
TS1: P1.2, P6.1, P6.4
TS2: P1.3, P6.3
TS3: P1.4, P6.2
TS4: P1.5, W1.3
TS5: P1.6, P4.1
TS6: P1.7, W1.1
TS7: P1.8, W1.2

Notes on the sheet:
LED
